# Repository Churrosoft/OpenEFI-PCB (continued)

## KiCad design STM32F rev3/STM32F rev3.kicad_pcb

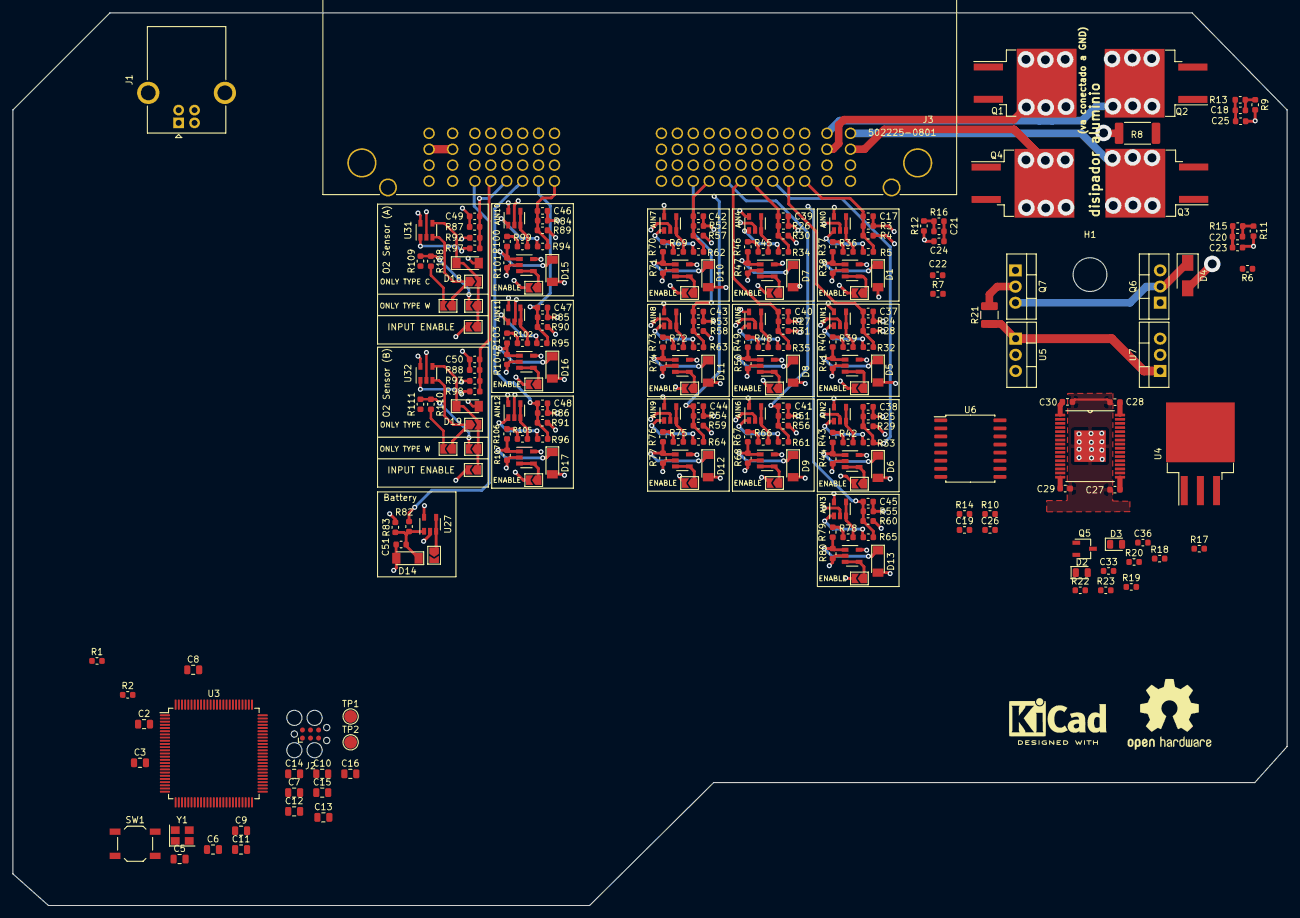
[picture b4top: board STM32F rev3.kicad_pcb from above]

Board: 4 copper layers, 200.2 x 140.2 mm, 248 parts (0 on the bottom side), 155 nets.

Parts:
C2, C3: 15pF; C_0805_2012Metric
C5, C9, C10, C11, C12, C13, C14, C15: 100nF; C_0805_2012Metric
C6: 1uF; C_0805_2012Metric
C7, C8: 2.2uF; C_0805_2012Metric
C16: 4.7uF; C_0805_2012Metric
C17, C37, C38, C39, C40, C41, C42, C43, C44, C45, C46, C47, C48, C49, C50, C51: 240pF; C_0603_1608Metric
C18, C19, C20, C21, C22: 10pF; C_0603_1608Metric
C23, C24, C25, C26, C27, C28, C29, C30: 10nF; C_0603_1608Metric
C33: 47nF; C_0603_1608Metric
C36: 0.1uF; C_0603_1608Metric
D1, D5, D6, D7, D8, D9, D10, D11, D12, D13, D14, D15, D16, D17, D18, D19: DZ2S033X0L; D_MiniMELF
D2, D3: 1N4148; D_0805_2012Metric
D4: SMAJ58CA; D_SMA
H1: MountingHole; MountingHole_5.3mm_M5
J1: USB_B; USB_B_OST_USB-B1HSxx_Horizontal
J2: Tag connect; Tag-Connect_TC2030-IDC-FP_2x03_P1.27mm_Vertical
J3: 502225-0801
JP1, JP2, JP3, JP4, JP5, JP6, JP7, JP8, JP9, JP10, JP11, JP12, JP13, JP14, JP15, JP16, JP17, JP18, JP19, JP20, JP21, JP22: Jumper_NC_Small; SolderJumper-2_P1.3mm_Open_TrianglePad1.0x1.5mm
LOGO1: Logo_Open_Hardware_Large; OSHW-Logo2_14.6x12mm_SilkScreen
Q1, Q2, Q3, Q4: ISL9V5045S3ST; TO-263-2
Q5: 2N3904; TSOT-23
Q6, Q7: IRF540N; TO-220-3_Vertical
R1, R2, R108, R109, R110, R111: 10k; R_0603_1608Metric
R3, R24, R25, R26, R27, R51, R52, R53, R54, R55, R84, R85, R86, R87, R88: 3.32k +-1%; R_0603_1608Metric
R4, R28, R29, R30, R31, R56, R57, R58, R59, R60, R89, R90, R91, R92, R93: 28.6k +-1%; R_0603_1608Metric
R5, R32, R33, R34, R35, R61, R62, R63, R64, R65, R94, R95, R96, R97, R98: 2.2k; R_0603_1608Metric
R6, R7: 100R; R_0603_1608Metric
R8: 0.02R; R_2512_6332Metric
R9, R10, R11, R12: 4.02k; R_0603_1608Metric
R13, R14, R15, R16: 36K; R_0603_1608Metric
R17: 10K 1/10W; R_0603_1608Metric
R18, R20: 10R 1/10W; R_0603_1608Metric
R19: 1M 1/10W; R_0603_1608Metric
R21: 0.01R; R_1210_3225Metric
R22: 57.6K 1/10W; R_0603_1608Metric
R23: 4.99K 1/10W; R_0603_1608Metric
R36, R39, R42, R45, R48, R66, R69, R72, R75, R78, R99, R102, R105: 16k 1/10W +-1%; R_0603_1608Metric
R37, R40, R43, R46, R49, R67, R70, R73, R76, R79, R100, R103, R106: 1k 1/10W +-1%; R_0603_1608Metric
R38, R41, R44, R47, R50, R68, R71, R74, R77, R80, R101, R104, R107: 33k 1/10W +-1%; R_0603_1608Metric
R82: 100k 1/10W +-1%; R_0603_1608Metric
R83: 20k 1/10W +-1%; R_0603_1608Metric
SW1: SW_Push; SW_SPST_TL3342
SYM1: SYM_Hot_Small; KiCad-Logo2_6mm_SilkScreen
TP1: BOOT0; TestPoint_Pad_D2.0mm
TP2: BOOT1; TestPoint_Pad_D2.0mm
U1: MCZ33810EK; SOP65P1030X245-33N
U2, U8, U9, U10, U11, U12, U13, U14, U15, U16, U17, U18, U19, U20, U21, U22, U23, U24, U25, U26, U27, U28, U29, U30, U31, U32, U33, U34, U35: LM321; SOT-23-5
U3: STM32F407VGTx; LQFP-100_14x14mm_P0.5mm
U4: MIC2940A-3.3WU; TO-263-3_TabPin2
U5, U7: MIC2940A-5.0WT; TO-220-3_Vertical
U6: LT4363IMS; SOIC-16W_7.5x10.3mm_P1.27mm
Y1: 25MHz; Crystal_SMD_3225-4Pin_3.2x2.5mm

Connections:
+3V3: C5.1, C6.1, C10.1, C11.1, C12.1, C13.1, C14.1, C15.1, C16.1, J2.1, U1.8, U3.6, U3.11, U3.19, U3.21, U3.22, U3.28, U3.50, U3.75, U3.100, U4.3
+5V: R4.2, R28.2, R29.2, R30.2, R31.2, R56.2, R57.2, R58.2, R59.2, R60.2, R89.2, R90.2, R91.2, R92.2, R93.2, U4.1, U5.3, U7.3, U12.5, U13.5, U14.5, U15.5, U16.5, U22.5, U23.5, U24.5, U25.5, U26.5, U27.5, U33.5, U34.5, U35.5
+12V: R21.1, R22.1, U1.25, U2.5, U5.1, U6.2, U7.1, U8.5, U9.5, U10.5, U11.5, U17.5, U18.5, U19.5, U20.5, U21.5, U28.5, U29.5, U30.5, U31.5, U32.5
+12VA: D2.2, J3.59, J3.60, Q5.1, Q6.3
/ECN1: U1.24, U3.60
/ECN2: U1.23, U3.61
/ECN3: U1.22, U3.62
/ECN4: U1.21, U3.5
/INY1: U1.10, U3.55
/INY2: U1.11, U3.56
/INY3: U1.12, U3.57
/INY4: U1.13, U3.58
/NRST: C9.2, J2.3, SW1.1, U3.14
/PMIC_CS: U1.4, U3.43
/PMIC_ENABLE: U1.9, U3.51, U3.59
/PMIC_SPARK: U1.20, U3.52
/RSN: R6.2, U1.27
/RSP: R7.2, U1.26
/SPI2_MISO: U1.7, U3.53
/SPI2_MOSI: U1.6, U3.54
/SPI2_SCK: U1.5, U3.47
/SYS_SWCLK: J2.4, U3.76
/SYS_SWDIO: J2.2, U3.72
/SYS_SWO: J2.6, U3.89
/Sensores/PC0: JP19.2, JP22.2
/Sheet5FA9324A/FB0: C18.2, R9.2, R13.1, U1.2
/Sheet5FA9324A/FB1: C19.2, R10.2, R14.1, U1.15
/Sheet5FA9324A/FB2: C20.2, R11.2, R15.1, U1.31
/Sheet5FA9324A/FB3: C21.2, R12.2, R16.1, U1.18
/Sheet5FA9324A/GD0: Q2.1, U1.3
/Sheet5FA9324A/GD1: Q1.1, U1.14
/Sheet5FA9324A/GD2: Q3.1, U1.30
/Sheet5FA9324A/GD3: Q4.1, U1.19
/USB_D+: J1.3, U3.71
/USB_D-: J1.2, U3.70
CONN_1: C30.2, J3.1, U1.1
CONN_2: C29.2, J3.2, U1.16
CONN_3: C17.1, J3.3, R3.1, R4.1, R5.2
CONN_4: C37.1, J3.4, R24.1, R28.1, R32.2
CONN_5: C38.1, J3.5, R25.1, R29.1, R33.2
CONN_6: C39.1, J3.6, R26.1, R30.1, R34.2
CONN_7: C40.1, J3.7, R27.1, R31.1, R35.2
CONN_8: C41.1, J3.8, R51.1, R56.1, R61.2
CONN_9: C42.1, J3.9, R52.1, R57.1, R62.2
CONN_10: C43.1, J3.10, R53.1, R58.1, R63.2
CONN_11: C44.1, J3.11, R54.1, R59.1, R64.2
CONN_12: C45.1, J3.12, R55.1, R60.1, R65.2
CONN_13: C46.1, J3.13, R84.1, R89.1, R94.2
CONN_14: C47.1, J3.14, R85.1, R90.1, R95.2
CONN_15: C48.1, J3.15, R86.1, R91.1, R96.2
CONN_16: C49.1, J3.16, R87.1, R92.1, R97.2
CONN_17: C50.1, J3.17, R88.1, R93.1, R98.2
CONN_18: J3.18, R82.2
CONN_21: C28.2, J3.21, U1.32
CONN_22: C27.2, J3.22, U1.17
CONN_41: C21.1, C24.1, J3.41, Q4.2, R16.2
CONN_42: C19.1, C26.1, J3.42, Q1.2, R14.2
CONN_61: C20.1, C23.1, J3.61, Q3.2, R15.2
CONN_62: C18.1, C25.1, J3.62, Q2.2, R13.2
GND: C2.2, C3.2, C5.2, C6.2, C7.2, C8.2, C9.1, C10.2, C11.2, C12.2, C13.2, C14.2, C15.2, C16.2, C17.2, C22.1, C23.2, C24.2, C25.2, C26.2, C27.1, C28.1, C29.1, C30.1, C33.2, C36.2, C37.2, C38.2, C39.2, C40.2, C41.2, C42.2, C43.2, C44.2, C45.2, C46.2, C47.2, C48.2, C49.2, C50.2, C51.2, D1.2, D3.2, D4.2, D5.2, D6.2, D7.2, D8.2, D9.2, D10.2, D11.2, D12.2, D13.2, D14.2, D15.2, D16.2, D17.2, D18.2, D19.2, J1.4, J2.5, J3.23, J3.24, J3.25, J3.26, J3.27, J3.28, J3.29, J3.30, J3.31, J3.32, J3.33, J3.34, J3.35, J3.36, J3.37, J3.38, J3.79, J3.80, R1.1, R2.2, R3.2, R6.1, R8.2, R9.1, R10.1, R11.1, R12.1, R23.1, R24.2, R25.2, R26.2, R27.2, R38.2, R41.2, R44.2, R47.2, R50.2, R51.2, R52.2, R53.2, R54.2, R55.2, R68.2, R71.2, R74.2, R77.2, R80.2, R83.2, R84.2, R85.2, R86.2, R87.2, R88.2, R101.2, R104.2, R107.2, R109.1, R111.1, SW1.2, U1.33, U2.2, U3.10, U3.20, U3.27, U3.74, U3.99, U4.2, U5.2, U6.9, U7.2, U8.2, U9.2, U10.2, U11.2, U12.2, U13.2, U14.2, U15.2, U16.2, U17.2, U18.2, U19.2, U20.2, U21.2, U22.2, U23.2, U24.2, U25.2, U26.2, U27.2, U28.2, U29.2, U30.2, U31.2, U32.2, U33.2, U34.2, U35.2, Y1.2, Y1.4
unnamed: C7.1, U3.49
unnamed: C8.1, U3.73
unnamed: C22.2, Q1.3, Q2.3, Q3.3, Q4.3, R7.1, R8.1
unnamed: C33.1, R19.1, R20.2, U6.4
unnamed: C36.1, U6.12
unnamed: C51.1, D14.1, R82.1, R83.1, U27.1
unnamed: D1.1, R37.1, R38.1, U12.1
unnamed: D2.1, Q5.2, R17.1
unnamed: D3.1, R17.2
unnamed: D4.1, Q6.2, Q7.3, U6.5
unnamed: D5.1, R40.1, R41.1, U13.1
unnamed: D6.1, R43.1, R44.1, U14.1
unnamed: D7.1, R46.1, R47.1, U15.1
unnamed: D8.1, R49.1, R50.1, U16.1
unnamed: D9.1, R67.1, R68.1, U22.1
unnamed: D10.1, R70.1, R71.1, U23.1
unnamed: D11.1, R73.1, R74.1, U24.1
unnamed: D12.1, R76.1, R77.1, U25.1
unnamed: D13.1, R79.1, R80.1, U26.1
unnamed: D15.1, R100.1, R101.1, U33.1
unnamed: D16.1, R103.1, R104.1, U34.1
unnamed: D17.1, R106.1, R107.1, U35.1
unnamed: D18.1, JP15.2, JP18.1, JP19.1, U31.4
unnamed: D19.1, JP16.2, JP21.1, JP22.1, U32.4
unnamed: J1.1, R1.2
unnamed: JP1.1, U13.3, U13.4
unnamed: JP2.1, U12.3, U12.4
unnamed: JP3.1, U14.3, U14.4
unnamed: JP4.1, U15.3, U15.4
unnamed: JP5.1, U16.3, U16.4
unnamed: JP6.1, U22.3, U22.4
unnamed: JP7.1, U23.3, U23.4
unnamed: JP8.1, U24.3, U24.4
unnamed: JP9.1, U25.3, U25.4
unnamed: JP10.1, U26.3, U26.4
unnamed: JP11.1, U27.3, U27.4
unnamed: JP12.1, U33.3, U33.4
unnamed: JP13.1, U34.3, U34.4
unnamed: JP14.1, U35.3, U35.4
unnamed: JP15.1, JP17.1, U31.3
unnamed: JP16.1, JP20.1, U32.3
unnamed: JP17.2, R108.2
unnamed: JP18.2, R108.1, R109.2
unnamed: JP20.2, R110.2
unnamed: JP21.2, R110.1, R111.2
unnamed: Q5.3, R18.2, R19.2
unnamed: Q6.1, R18.1
unnamed: Q7.1, R20.1
unnamed: Q7.2, R21.2, U6.3
unnamed: R2.1, TP1.1, U3.94
unnamed: R5.1, U2.1
unnamed: R22.2, R23.2, U6.1
unnamed: R32.1, U8.1
unnamed: R33.1, U9.1
unnamed: R34.1, U10.1
unnamed: R35.1, U11.1
unnamed: R36.1, U2.3, U2.4
unnamed: R36.2, R37.2
unnamed: R39.1, U8.3, U8.4
unnamed: R39.2, R40.2
unnamed: R42.1, U9.3, U9.4
unnamed: R42.2, R43.2
unnamed: R45.1, U10.3, U10.4
unnamed: R45.2, R46.2
unnamed: R48.1, U11.3, U11.4
unnamed: R48.2, R49.2
unnamed: R61.1, U17.1
unnamed: R62.1, U18.1
unnamed: R63.1, U19.1
unnamed: R64.1, U20.1
unnamed: R65.1, U21.1
unnamed: R66.1, U17.3, U17.4
unnamed: R66.2, R67.2
unnamed: R69.1, U18.3, U18.4
unnamed: R69.2, R70.2
unnamed: R72.1, U19.3, U19.4
unnamed: R72.2, R73.2
unnamed: R75.1, U20.3, U20.4
unnamed: R75.2, R76.2
unnamed: R78.1, U21.3, U21.4
unnamed: R78.2, R79.2
unnamed: R94.1, U28.1
unnamed: R95.1, U29.1
unnamed: R96.1, U30.1
unnamed: R97.1, U31.1
unnamed: R98.1, U32.1
unnamed: R99.1, U28.3, U28.4
unnamed: R99.2, R100.2
unnamed: R102.1, U29.3, U29.4
unnamed: R102.2, R103.2
unnamed: R105.1, U30.3, U30.4
unnamed: R105.2, R106.2
unnamed: TP2.1, U3.37
OSC_IN: C2.1, U3.12, Y1.1
OSC_OUT: C3.1, U3.13, Y1.3

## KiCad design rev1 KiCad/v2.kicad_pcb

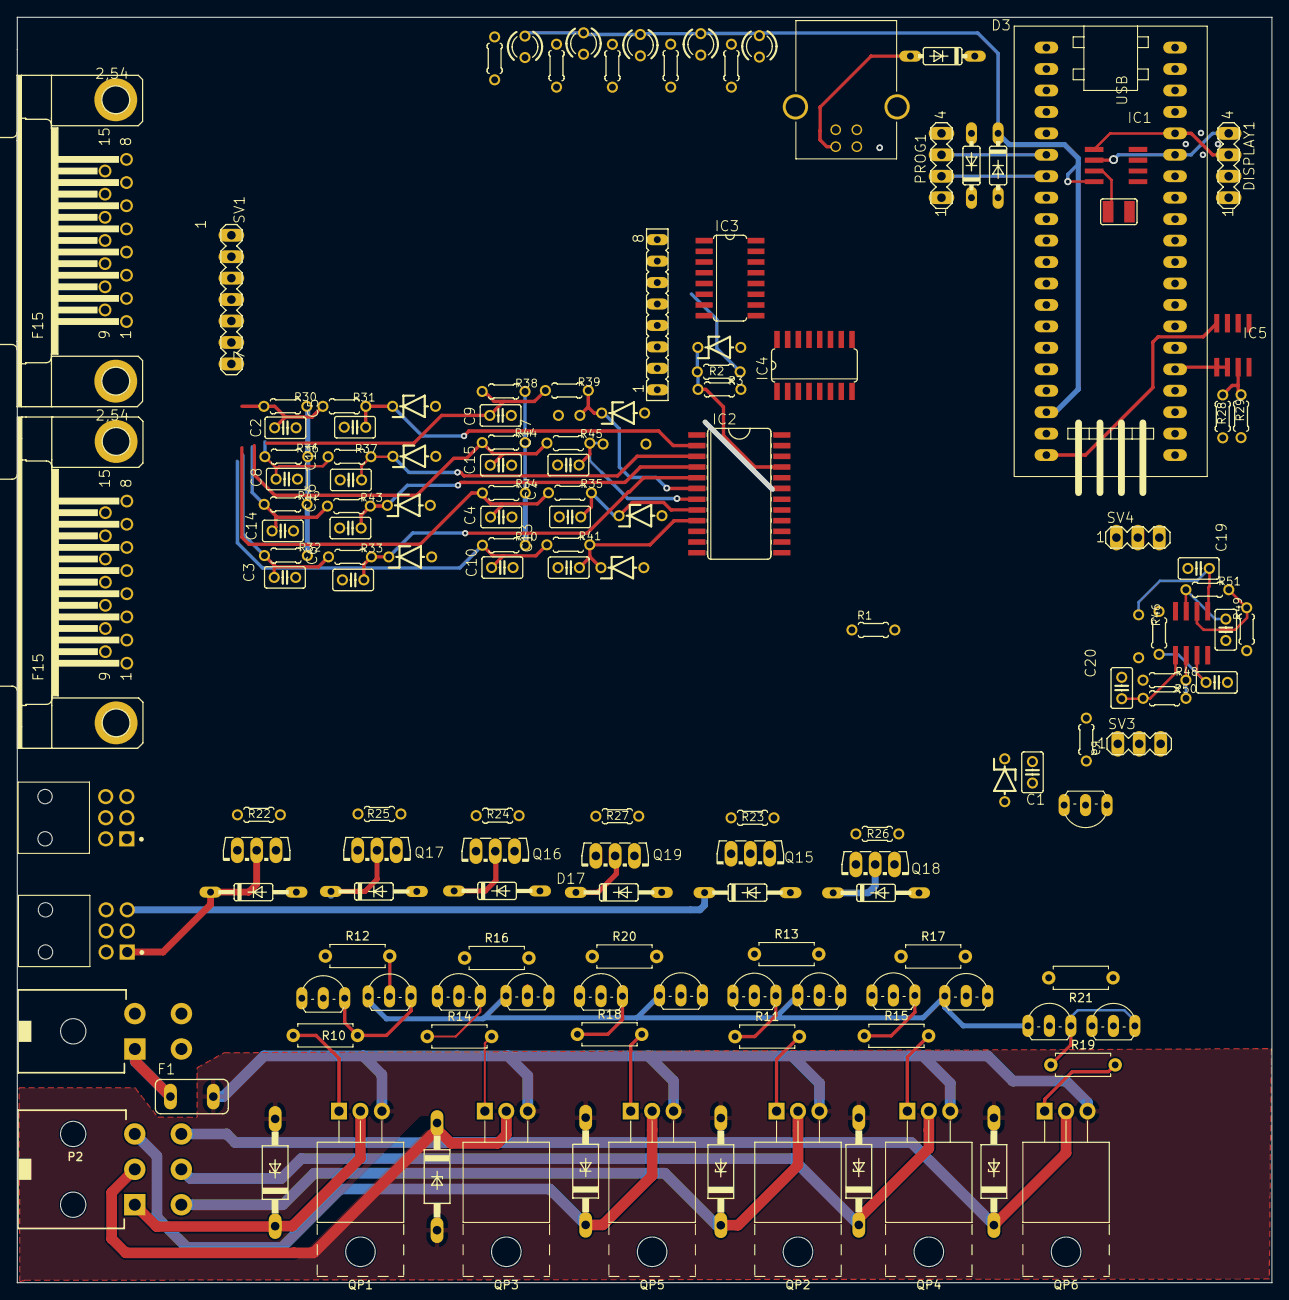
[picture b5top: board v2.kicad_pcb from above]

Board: 4 copper layers, 148.6 x 149.9 mm, 149 parts (0 on the bottom side), 101 nets.

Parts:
C1: 0.1uf; C025-025X050
C2, C3, C4, C8, C9, C10, C14, C15: 0.001uF; C025-025X050
C5, C6, C7, C11, C12, C13, C16, C17: C-EU025-025X050; C025-025X050
C18, C19: 0.001uf; C025-025X050
C20, C21: 0.22uf; C025-025X050
D1, D2, D3: 1N4148DO35-7; DO35-7
D4, D5, D18, D19, D20, D21, D22, D23, D24, D25: 5.1v; ZDIO-5
D6, D7, D8, D9, D10, D11: BZY97; F126Z12
D12, D13, D14, D15, D16, D17: 1N4446; DO35-10
DISPLAY1: MA04-1
F1: TE5
IC1: 24SN; SO-08
IC2: 4067D; SO24W
IC3, IC4: 74595D; SO16
IC5, IC6: LM358D; SO08
J1, J2: 1053141206; MOLEX_1053141206
LED1, LED2, LED3, LED4, LED5: LED3MM
P1: 39-30-?04?
P2: 39-30-?06?
PROG1: MA04-1
Q1, Q2, Q4, Q6, Q8, Q10, Q12: BC548; TO92-EBC
Q3, Q5, Q7, Q9, Q11, Q13: BC558; TO92-EBC
Q14, Q15, Q16, Q17, Q18, Q19: BD139; TO126AV
QP1, QP2, QP3, QP4, QP5, QP6: IRLZ44N; TO-220-3_Horizontal_TabUp
R1, R4, R5, R6, R7, R8, R9, R22, R23, R24, R25, R26, R27, R29, R48, R49: 1k; 0204_5
R2: 15k; 0204_5
R3: 5k; 0204_5
R10, R11, R12, R13, R14, R15, R16, R17, R18, R19, R20, R21: R_Small; R_Axial_DIN0207_L6.3mm_D2.5mm_P7.62mm_Horizontal
R28, R46, R47: 2k; 0204_5
R30, R31, R32, R33, R34, R35, R36, R37, R38, R39, R40, R41, R42, R43, R44, R45: R-US_0204_5; 0204_5
R50, R51: 1.5k; 0204_5
SJ1: SJW
SV1: MA07-1
SV2: FE08-1; FE08
SV3, SV4: MA03-1
U$1: STM32F103C8T6-MODULE
X1: MINI-USB_4P-85-32004-10X; 85-32004-10X
X2, X3: F15HP

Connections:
3V3: IC5.8, U$1.3.3V_1
5V: D2.A, DISPLAY1.2, IC2.24, IC3.16, IC4.16, IC6.8, R30.1, R32.1, R34.1, R36.1, R38.1, R40.1, R42.1, R44.1, SV2.8, SV3.3, SV4.3
/IO Principal/RCK: IC3.12, IC4.12
/IO Principal/SCK2: IC3.11, IC4.11
/Sensores/AIN2: C14.1, R42.2, R43.2
/Sensores/AIN3: C3.1, R32.2, R33.2
/Sensores/AIN5: C15.1, R44.2, R45.2
/Sensores/AIN6: C4.1, R34.2, R35.2
/Sensores/AIN7: C10.1, R40.2, R41.2
/v2_1/5V1: D1.C, D2.C, D3.C, IC1.8, LED1.A, LED2.A, LED3.A, LED4.A, LED5.A, U$1.5V
/v2_1/5V-USB: D3.A, X1.1
/v2_1/D+: U$1.PA_12, X1.3
/v2_1/D-: U$1.PA_11, X1.2
/v2_1/L5: R8.1, U$1.PA_5
/v2_1/RX: PROG1.3, U$1.PA_9
/v2_1/TX: PROG1.2, U$1.PA_10
A: IC2.10, U$1.PB_1
A0: IC2.1, R28.1
A1: IC5.1, IC5.2, U$1.PA_0
ACC: Q2.C, Q4.C, Q6.C, Q8.C, Q10.C, Q12.C, R2.2, SV2.7
AIN0: C2.1, R30.2, R31.2
AIN1: C8.1, R36.2, R37.2
AIN4: C9.1, R38.2, R39.2
AOUT0: C5.1, D18.C, IC2.2, R31.1
AOUT1: C11.1, D21.C, IC2.3, R37.1
AOUT2: C16.1, D24.C, IC2.4, R43.1
AOUT3: C6.1, D19.C, IC2.5, R33.1
AOUT4: C12.1, D22.C, IC2.6, R39.1
AOUT5: C17.1, D25.C, IC2.7, R45.1
AOUT6: C7.1, D20.C, IC2.8, R35.1
AOUT7: C13.1, D23.C, IC2.9, R41.1
B: IC2.11, U$1.PB_0
C: IC2.14, U$1.PA_7
D: IC2.13, U$1.PA_6
GNC/GLP_MODE: C1.1, D5.C
GND: C1.2, C2.2, C3.2, C4.2, C5.2, C6.2, C7.2, C8.2, C9.2, C10.2, C11.2, C12.2, C13.2, C14.2, C15.2, C16.2, C17.2, C18.2, C19.2, C20.2, C21.2, D4.A, D5.A, D12.A, D14.A, D15.A, D16.A, D17.A, D18.A, D19.A, D20.A, D21.A, D22.A, D23.A, D24.A, D25.A, DISPLAY1.1, F1.1, IC1.1, IC1.2, IC1.3, IC1.4, IC2.12, IC2.15, IC3.8, IC3.10, IC3.13, IC4.8, IC4.10, IC4.13, IC5.4, IC6.4, P1.1, P1.2, P1.3, P1.4, PROG1.1, Q1.E, Q3.C, Q5.C, Q7.C, Q9.C, Q11.C, Q13.C, Q14.E, Q15.E, Q16.E, Q17.E, Q18.E, Q19.E, R3.1, R29.1, R48.2, R49.2, SJ1.2, SV2.1, SV2.2, SV3.1, SV4.1, U$1.GND_1, U$1.GND_2, U$1.GND_3, X1.4
GND2: D6.A, D7.A, D8.A, D9.A, D10.A, D11.A, F1.2, QP1.3, QP2.3, QP3.3, QP4.3, QP5.3, QP6.3
INY1: D6.C, P2.1, QP1.2
INY2: D8.C, P2.2, QP3.2
INY3: D10.C, P2.3, QP5.2
INY4: D7.C, P2.4, QP2.2
INY5: D9.C, P2.5, QP4.2
INY6: D11.C, P2.6, QP6.2
LAMB0OUT: C20.1, IC2.23, IC6.1, R50.2
LAMB1OUT: C21.1, IC2.22, IC5.7, R51.2
M1: IC3.15, SV2.6
M2: IC3.1, SV2.5
M3: IC3.2, SV2.4
M4: IC3.3, SV2.3
unnamed: C18.1, IC6.3, R46.2
unnamed: C19.1, IC5.5, R47.2
unnamed: D1.A, PROG1.4
unnamed: IC1.7, SJ1.1
unnamed: IC3.9, IC4.14
unnamed: IC5.3, R28.2, R29.2
unnamed: IC5.6, R49.1, R51.1
unnamed: IC6.2, R48.1, R50.1
unnamed: LED1.K, R4.2
unnamed: LED2.K, R5.2
unnamed: LED3.K, R6.2
unnamed: LED4.K, R7.2
unnamed: LED5.K, R8.2
unnamed: Q1.B, R9.2
unnamed: Q2.B, Q3.B, R12.2
unnamed: Q2.E, Q3.E, R10.1
unnamed: Q4.B, Q5.B, R13.2
unnamed: Q4.E, Q5.E, R11.1
unnamed: Q6.B, Q7.B, R16.2
unnamed: Q6.E, Q7.E, R14.1
unnamed: Q8.B, Q9.B, R17.2
unnamed: Q8.E, Q9.E, R15.1
unnamed: Q10.B, Q11.B, R20.2
unnamed: Q10.E, Q11.E, R18.1
unnamed: Q12.B, Q13.B, R21.2
unnamed: Q12.E, Q13.E, R19.1
unnamed: Q14.B, R22.2
unnamed: Q15.B, R23.2
unnamed: Q16.B, R24.2
unnamed: Q17.B, R25.2
unnamed: Q18.B, R26.2
unnamed: Q19.B, R27.2
unnamed: QP1.1, R10.2
unnamed: QP2.1, R11.2
unnamed: QP3.1, R14.2
unnamed: QP4.1, R15.2
unnamed: QP5.1, R18.2
unnamed: QP6.1, R19.2
RL1: IC3.4, R22.1
RL1IN: D12.C, J1.1, Q14.C
RL2: IC3.5, R24.1
RL2IN: D14.C, J1.2, Q16.C
RL3: IC3.6, R23.1
RL3IN: D13.C, J1.3, Q15.C
RL4: IC3.7, R25.1
RL4IN: D15.C, J1.4, Q17.C
RL5: IC4.15, R27.1
RL5IN: D17.C, J1.5, Q19.C
RL6IN: D16.C, J1.6, Q18.C
SCL: DISPLAY1.4, IC1.6, U$1.PB_10
SDA: DISPLAY1.3, IC1.5, U$1.PB_11
VBAT: D4.C, IC2.21, R2.1, R3.2

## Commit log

2019-04-16 agregado de placas ya existentes
2019-04-19 Variante nueva!!
    Nueva variente de la placa basada en STM32F, se agrego un AtMega328 que va a correr una version modificada de OpenEFI para manejar las salidas e inyectores, ademas se agregaron mas pines de E/S se ca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
2019-04-27 Creacion de V2 del PCB para SMT32F
2019-04-29 cambios menores
2019-04-30 Avances en I/O en rev1
2020-10-03 init v3
2020-10-12 WIP v3 on STM32
2020-11-08 sacando porquerias
2020-11-08 V3 WIP
2020-11-08 el ci ameo'
2020-11-08 los espacios me dan ansiedad
2020-11-08 fix submodules/ pipeline config
2020-11-08 update paths
2020-11-08 fix drc error
2020-11-08 add submodule
2020-11-08 minor fix
2020-11-14 WIP V3
2020-11-26 Update on PMIC
2020-12-08 GPIO
2020-12-27 WIP: PAP Driver
2021-04-01 Last commit to rev3
2021-04-08 uEFI v2.x
2021-04-08 Update git submodules for uEFI
2021-04-10 Making sensor board easier to assemble
2021-04-21 uEFI v2 beta release
2022-01-10 bump to kicad 6, init uEFI v3
2022-02-05 move old boards to __old
2022-02-05 updated github workflows
2022-02-06 fix release type
2022-02-06 bump kibot version
2022-02-06 minor update
2022-02-06 remove InteractiveHtmlBom
2022-02-06 ssh => https submodule
2022-02-06 update v3 pcb libs
2022-02-12 rev3, analog inputs
2022-02-13 rev3 ADC SPI
2022-02-13 rev3, connect PMIC to injector outs
2022-02-18 rev3, PMIC, Relays done
2022-02-18 rev3, jtag
2022-02-18 rev3, complete routing, ERC
2022-02-19 rev3, added acc detect
2022-03-03 fix 10k res
2022-03-24 update kicad_prl
2022-03-24 updated release workflow
2022-03-24 fix release.yml
2022-03-30 added actions, update old files to kicad 6
2022-03-30 branding, fix memory footprint
2022-03-30 added kicad_common
2022-03-30 fix date/version
2022-03-30 revert date autofill
2022-04-13 update jlcpcb kibot
2022-05-01 uEFI rev 3.1.0
2022-05-05 wip v3.1
2022-05-07 Added connector for uEFI
2022-09-24 add ckp sensor setup
2022-09-27 uEFI rev 3.1
2022-09-27 fix? cicd
2022-09-27 change image to v2_k6
2022-09-27 fix dockerhub tag image
2022-09-27 add kibot config files
2022-09-27 test pass config to makefile
2022-09-27 fix config path
2022-09-27 enable verbose logs en kibot
2022-09-28 remove ERC Workflow
2022-09-29 Update LICENSE
2022-09-29 uEFI r3.2
2022-10-12 uEFI rev 3.3
2022-10-25 pre-production files, uEFI v3.4
2022-11-12 fix bom output
2023-01-19 AA wiring, lib&connector update, added eggbug
2023-01-23 Fix SPI pad & connector, add new images, Co-authored-by: Lucacik <name@example.com>
2023-03-04 fix relay tracks
2023-07-01 uEFI v3, fix 12v => 5v overcurrent issue
2023-10-07 rev4 init
2023-10-07 import PCB outline from rusEFI / hellen board
2023-10-09 wip PMIC on rev4 board
2023-10-13 changes on sensors sch
2023-10-14 wip sensors pinout:
2023-10-14 update sensors/connector pinout, added rtc vbatt backup
2023-10-19 WIP Analog frontend
2023-10-19 WIP analog frontend, init ckp"
2023-10-20 WIP relay driver
2023-10-22 WIP CKP/CMP
2023-10-22 fix board errors
2023-10-22 add tacho driver
2023-10-23 wip SD card
2023-10-28 wip relay pcb
2023-11-01 WIP SPI
2023-11-02 fix pcb size/wideband
2023-11-11 WIP Rev4 SPI
2023-11-11 Rev4: add all MCU signals
2023-11-11 Rev4 fix DRC errors
2023-11-12 Rev4 WIP LCSC assigments
2023-12-05 update footprints
2024-04-07 update 32khz crystal
